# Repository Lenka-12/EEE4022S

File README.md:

# Audio Digitisation System 🎵

A high-performance audio digitization system built around the STM32F7 microcontroller, featuring dual Delta-Sigma ADCs (PCM1808 and ADAU1978) and an integrated ADC for comprehensive audio capture.

## 🎯 Overview

This project implements a complete audio digitization pipeline that captures audio data through multiple ADCs and transmits it to a PC for MATLAB-based analysis.

## 🔧 Hardware Components

### STM32F7 Nucleo Board
- Main processing unit
- Handles ADC interfacing and USB communication

### PCM1808 Delta-Sigma ADC ([Buy](https://www.aliexpress.com/item/32777376004.html))
- Stereo Audio ADC configuration
- Input: Bottom port MEMS microphone from DEVKIT-MEMS-001
- Signal conditioning via AD828 op-amp module ([AD828 Module Source](https://www.robotics.org.za/AD828A))
- I2S interface via SAI1 Block B
- 48 kHz sampling rate
- DMA circular mode operation

### Integrated ADC
- Input: Nucleo board pin A3
- Signal from top port MEMS microphone (DEVKIT-MEMS-001)
- Signal conditioning via BOB-09816 ([SparkFun BOB-09816](https://www.sparkfun.com/products/9816))
- Timer-triggered operation
- Circular DMA mode

### ADAU1978 Delta-Sigma ADC
- Integrated via [STEVAL-STWINMAV1](https://www.st.com/en/evaluation-tools/steval-stwinmav1.html) module
- TDM4 protocol through SAI1 Block A
- 24-bit resolution at 48 kHz
- DMA circular mode operation

> **Important Note**: When configuring SAI for TDM:
> - Clock strobing must be set to rising edge
> - Frame Synchro offset must be set before the First Bit

## 🔌 Communication

### USB Interface
- Protocol: USB Full Speed (FS) CDC
- Data transmission triggered by user button
- ADC activation controlled via Python script commands

## 💡 Status Indicators

| LED  | Function |
|------|----------|
| LD1  | Integrated ADC active |
| LD2  | PCM1808 active |
| LD3  | ADAU1978 active |

## 🛠️ Hardware Sources

### Microphones
- [DEVKIT-MEMS-001](https://www.sameskydevices.com/product/audio/microphones/development-kits/devkit-mems-001)
  - Bottom port MEMS mic → PCM1808
  - Top port MEMS mic → Integrated ADC

### Signal Conditioning
- PCM1808: [AD828 Op-amp Module](https://www.robotics.org.za/AD828A)
- Integrated ADC: [BOB-09816](https://www.sparkfun.com/products/9816)

### ADC Modules
- [PCM1808 Stereo Delta-Sigma ADC](https://www.aliexpress.com/item/32777376004.html)
- [STEVAL-STWINMAV1](https://www.st.com/en/evaluation-tools/steval-stwinmav1.html) (ADAU1978)
- STM32F7 Integrated ADC

## 📝 PCB Documentation

The repository includes:
- STEVAL-STWINMAV1 module adapter designs
- Audio Digitisation Hardware based on PCM1862 (production pending)
- 
## 📊 Data Analysis

MATLAB scripts are provided for processing the captured audio data. See the `/Processing` directory for analysis tools.

## 🤝 Contributing

Contributions are welcome! Please read our [Contributing Guide](CONTRIBUTING.md) for details on our code of conduct and the process for submitting pull requests.

## 📄 License

This project is licensed under the MIT License - see the [LICENSE](LICENSE) file for details.

## ✨ Acknowledgments

- STMicroelectronics for the STEVAL-STWINMAV1 reference design
- Same Sky for DEVKIT-MEMS-001
- SparkFun Electronics for BOB-09816
- Contributors and testers

---
*For technical questions and support, please open an issue in the repository.*

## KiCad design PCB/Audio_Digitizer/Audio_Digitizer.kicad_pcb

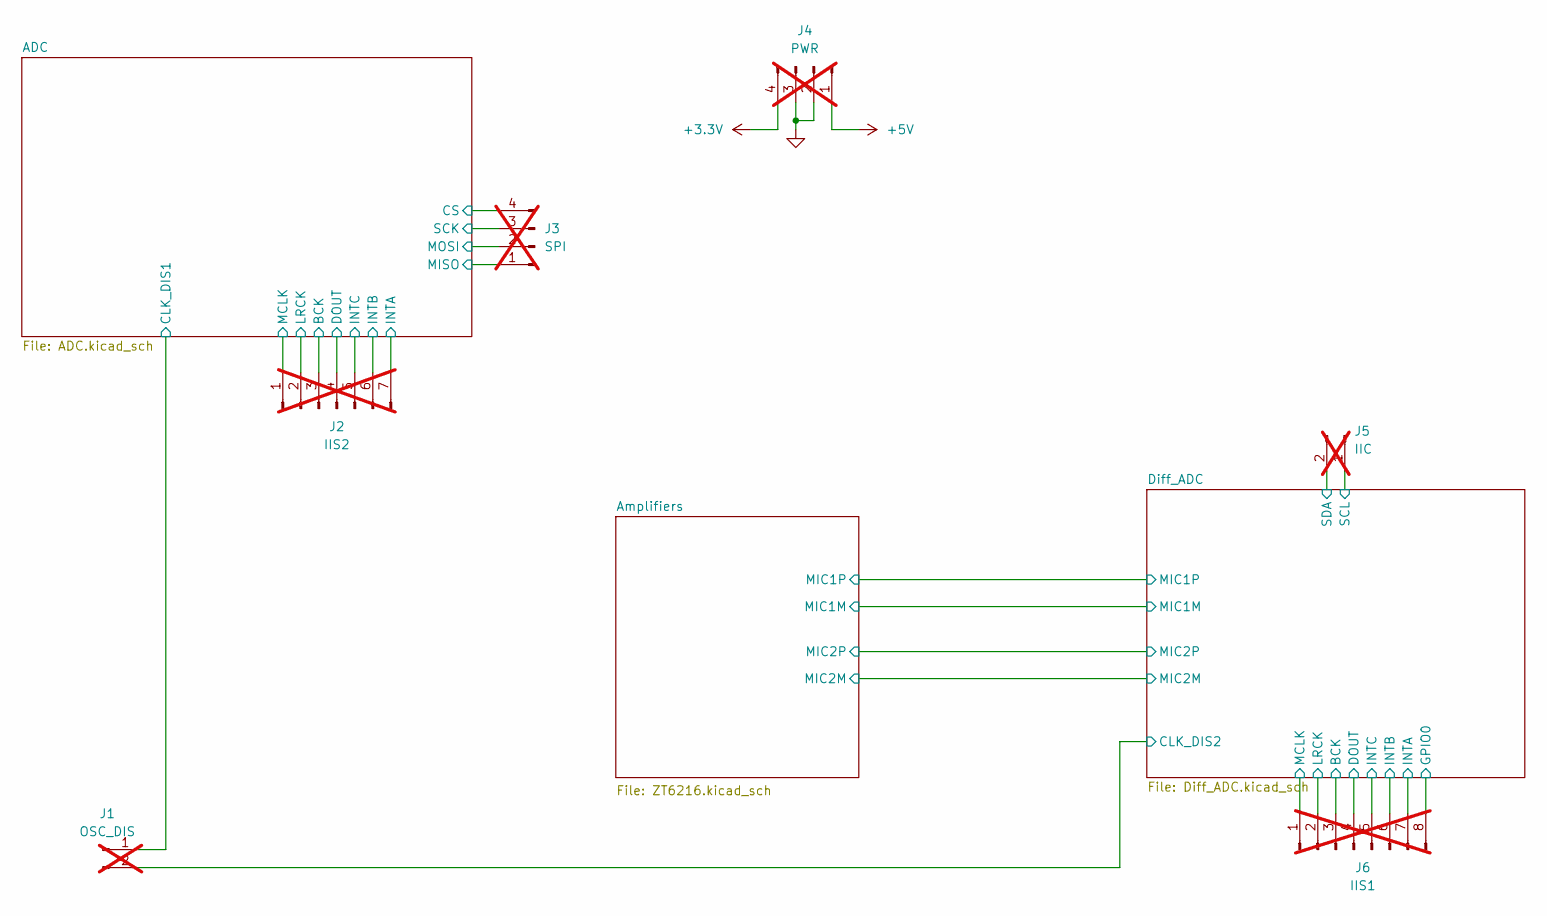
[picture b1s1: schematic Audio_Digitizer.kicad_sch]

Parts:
J1: OSC_DIS; PinHeader_1x02_P2.54mm_Vertical; not fitted
J2: IIS2; PinHeader_1x07_P2.54mm_Vertical; not fitted
J3: SPI; PinHeader_1x04_P2.54mm_Vertical; not fitted
J4: PWR; PinHeader_1x04_P2.54mm_Vertical; not fitted
J5: IIC; PinHeader_1x02_P2.54mm_Vertical; not fitted
J6: IIS1; PinHeader_1x08_P2.54mm_Vertical; not fitted

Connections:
+3.3V: J4.4; also elsewhere on the board
+5V: J4.1; also elsewhere on the board
/ADC/BCK: J2.3; also elsewhere on the board
/ADC/CLK_DIS1: J1.1; also elsewhere on the board
/ADC/CS: J3.4; also elsewhere on the board
/ADC/DOUT: J2.4; also elsewhere on the board
/ADC/INTA: J2.7; also elsewhere on the board
/ADC/INTB: J2.6; also elsewhere on the board
/ADC/INTC: J2.5; also elsewhere on the board
/ADC/LRCK: J2.2; also elsewhere on the board
/ADC/MCLK: J2.1; also elsewhere on the board
/ADC/MISO: J3.1; also elsewhere on the board
/ADC/MOSI: J3.2; also elsewhere on the board
/ADC/SCK: J3.3; also elsewhere on the board
/Diff_ADC/BCK: J6.3; also elsewhere on the board
/Diff_ADC/CLK_DIS2: J1.2; also elsewhere on the board
/Diff_ADC/DOUT: J6.4; also elsewhere on the board
/Diff_ADC/GPIO0: J6.8; also elsewhere on the board
/Diff_ADC/INTA: J6.7; also elsewhere on the board
/Diff_ADC/INTB: J6.6; also elsewhere on the board
/Diff_ADC/INTC: J6.5; also elsewhere on the board
/Diff_ADC/LRCK: J6.2; also elsewhere on the board
/Diff_ADC/MCLK: J6.1; also elsewhere on the board
/Diff_ADC/SCL: J5.1; also elsewhere on the board
/Diff_ADC/SDA: J5.2; also elsewhere on the board
GND: J4.2, J4.3; also elsewhere on the board

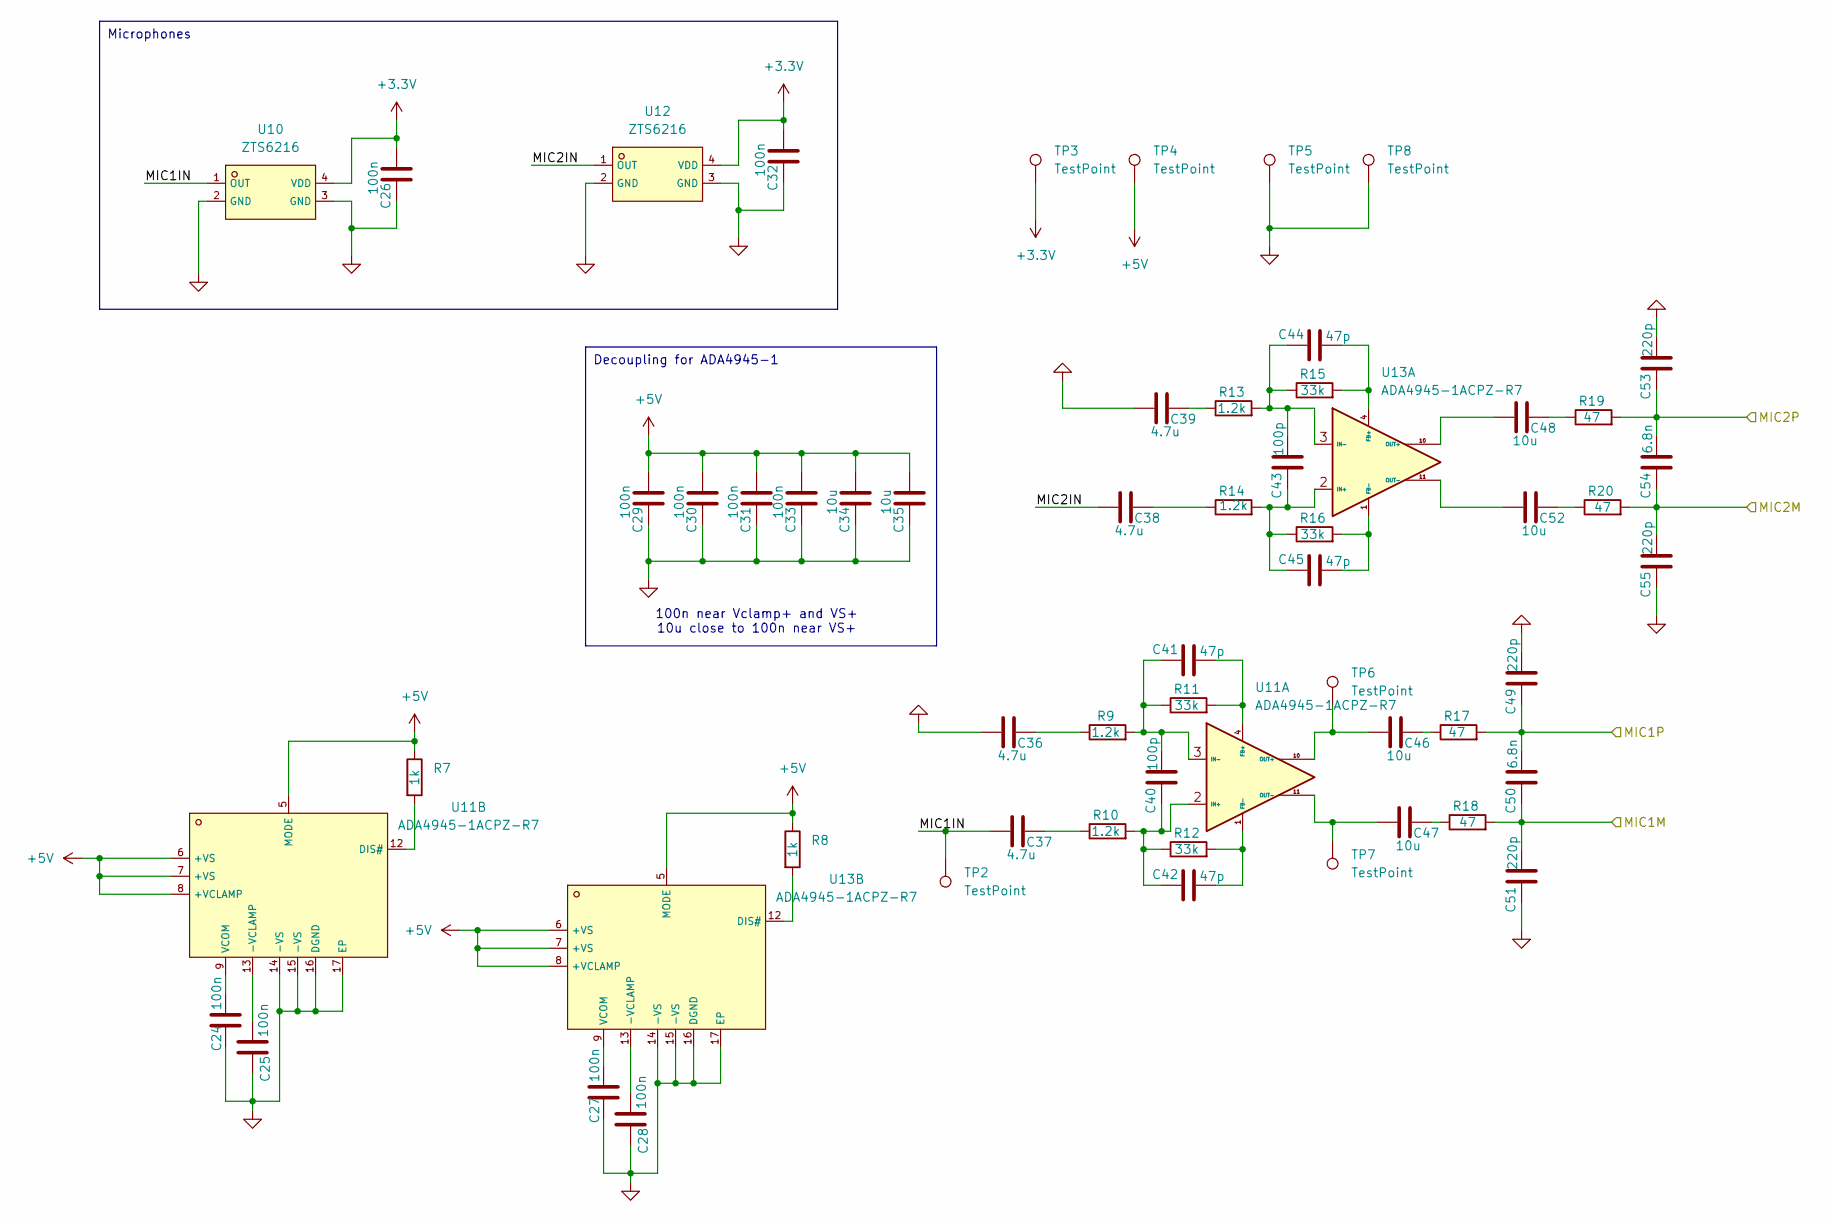
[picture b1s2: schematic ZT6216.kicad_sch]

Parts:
C24, C25, C26, C27, C28, C29, C30, C31, C32, C33: 100n; C_0402_1005Metric
C34, C35, C46, C47, C48, C52: 10u; C_0603_1608Metric
C36, C37, C38, C39: 4.7u; C_0402_1005Metric
C40, C43: 100p; C_0402_1005Metric
C41, C42, C44, C45: 47p; C_0402_1005Metric
C49, C51, C53, C55: 220p; C_0402_1005Metric
C50, C54: 6.8n; C_0603_1608Metric
R7, R8: 1k; R_0603_1608Metric
R9, R10, R13, R14: 1.2k; R_0402_1005Metric
R11, R12, R15, R16: 33k; R_0402_1005Metric
R17, R18, R19, R20: 47; R_0402_1005Metric
TP2, TP3, TP4, TP5, TP6, TP7, TP8: TestPoint; TestPoint_Pad_D1.5mm
U10, U12: ZTS6216; MIC-SMD_4P-L2.8-W1.9-P1.84-TL; LCSC C481302
U11, U13: ADA4945-1ACPZ-R7; LFCSP-16-1EP_3x3mm_P0.5mm_EP1.6x1.6mm; LCSC C560261

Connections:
+3.3V: C26.1, C32.1, TP3.1, U10.4 (VDD), U12.4 (VDD); also elsewhere on the board
+5V: C29.1, C30.1, C31.1, C33.1, C34.1, C35.1, R7.1, R8.1, TP4.1, U11.5 (MODE), U11.6 (+VS), U11.7 (+VS), U11.8 (+VCLAMP), U13.5 (MODE), U13.6 (+VS), U13.7 (+VS), U13.8 (+VCLAMP); also elsewhere on the board
/Amplifiers/MIC1IN: C37.1, TP2.1, U10.1 (OUT)
/Amplifiers/MIC1M: C50.1, C51.2, R18.2; also elsewhere on the board
/Amplifiers/MIC1P: C49.1, C50.2, R17.2; also elsewhere on the board
/Amplifiers/MIC2IN: C38.1, U12.1 (OUT)
/Amplifiers/MIC2M: C54.1, C55.2, R20.2; also elsewhere on the board
/Amplifiers/MIC2P: C53.1, C54.2, R19.2; also elsewhere on the board
GND: C24.1, C25.1, C26.2, C27.1, C28.1, C29.2, C30.2, C31.2, C32.2, C33.2, C34.2, C35.2, C36.1, C39.1, C49.2, C51.1, C53.2, C55.1, TP5.1, TP8.1, U10.2 (GND), U10.3 (GND), U11.14 (-VS), U11.15 (-VS), U11.16 (DGND), U11.17 (EP), U12.2 (GND), U12.3 (GND), U13.14 (-VS), U13.15 (-VS), U13.16 (DGND), U13.17 (EP); also elsewhere on the board
unnamed: C36.2, R9.1
unnamed: C37.2, R10.1
unnamed: C38.2, R14.1
unnamed: C39.2, R13.1
unnamed: C46.2, R17.1
unnamed: C47.2, R18.1
unnamed: C48.2, R19.1
unnamed: C52.2, R20.1
unnamed: C41.2, R11.2, U11.4 (FB+)
unnamed: C42.2, R12.2, U11.1 (FB-)
unnamed: C40.1, C42.1, R10.2, R12.1, U11.2 (IN+)
unnamed: C40.2, C41.1, R9.2, R11.1, U11.3 (IN-)
unnamed: C46.1, TP6.1, U11.10 (OUT+)
unnamed: C47.1, TP7.1, U11.11 (OUT-)
unnamed: C25.2, U11.13 (-VCLAMP)
unnamed: R7.2, U11.12 (DIS#)
unnamed: C24.2, U11.9 (VCOM)
unnamed: C44.2, R15.2, U13.4 (FB+)
unnamed: C45.2, R16.2, U13.1 (FB-)
unnamed: C43.1, C45.1, R14.2, R16.1, U13.2 (IN+)
unnamed: C43.2, C44.1, R13.2, R15.1, U13.3 (IN-)
unnamed: C48.1, U13.10 (OUT+)
unnamed: C52.1, U13.11 (OUT-)
unnamed: C28.2, U13.13 (-VCLAMP)
unnamed: R8.2, U13.12 (DIS#)
unnamed: C27.2, U13.9 (VCOM)

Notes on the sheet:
Decoupling for ADA4945-1
Microphones
100n near Vclamp+ and VS+ 10u close to 100n near VS+

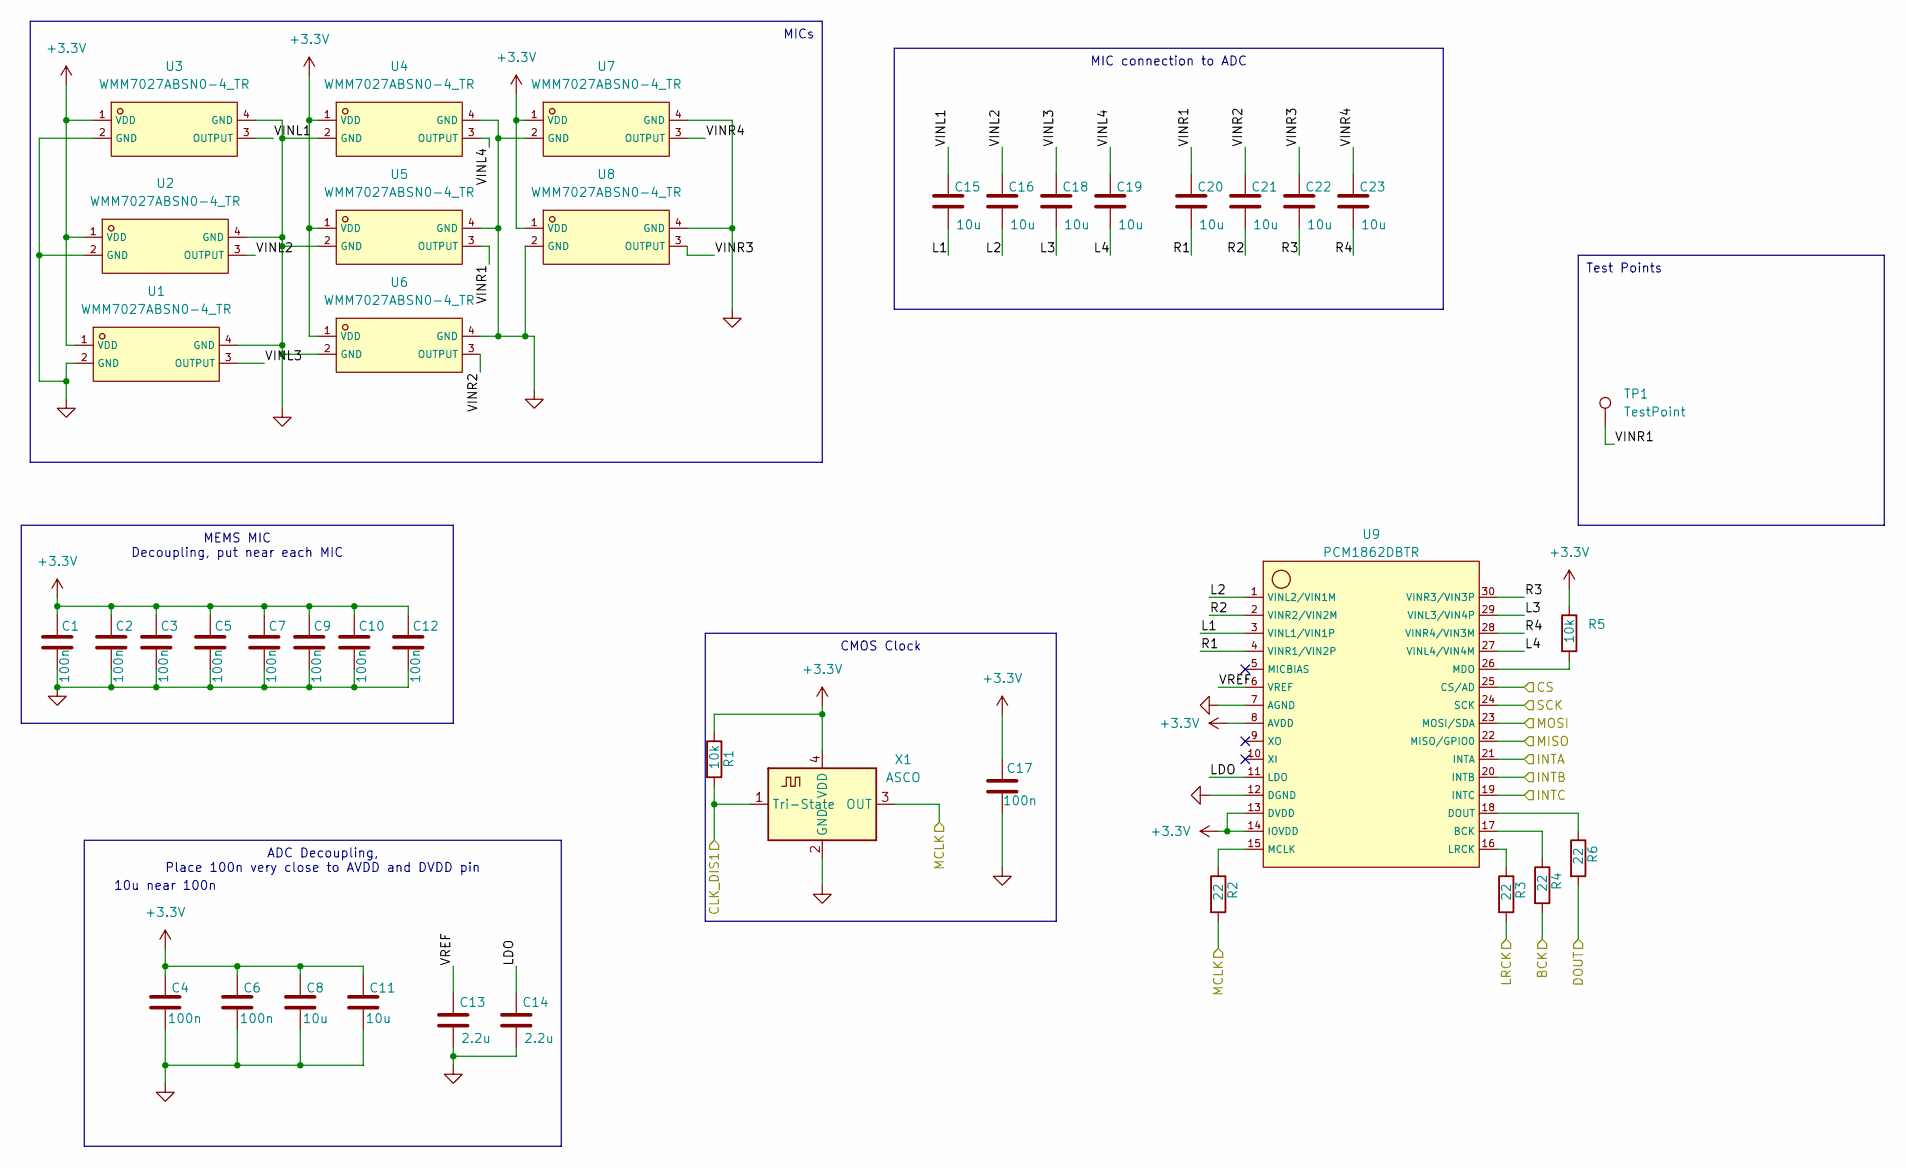
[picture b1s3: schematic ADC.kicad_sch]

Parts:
C1, C2, C3, C4, C5, C6, C7, C9, C10, C12, C17: 100n; C_0402_1005Metric
C8, C11, C15, C16, C18, C19, C20, C21, C22, C23: 10u; C_0603_1608Metric
C13, C14: 2.2u; C_0603_1608Metric
R1, R5: 10k; R_0402_1005Metric
R2, R3, R4, R6: 22; R_0402_1005Metric
TP1: TestPoint; TestPoint_Pad_D1.5mm
U1, U2, U3, U4, U5, U6, U7, U8: WMM7027ABSN0-4_TR; MIC-SMD_4P-L2.8-W1.9_MSM38A2718Z9BM3; LCSC C2931972
U9: PCM1862DBTR; TSSOP-30_4.4x7.8mm_P0.5mm
X1: ASCO; Crystal_SMD_3225-4Pin_3.2x2.5mm

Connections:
+3.3V: C1.1, C2.1, C3.1, C4.1, C5.1, C6.1, C7.1, C8.1, C9.1, C10.1, C11.1, C12.1, C17.1, R1.1, R5.1, U1.1 (VDD), U2.1 (VDD), U3.1 (VDD), U4.1 (VDD), U5.1 (VDD), U6.1 (VDD), U7.1 (VDD), U8.1 (VDD), U9.8 (AVDD), U9.13 (DVDD), U9.14 (IOVDD), X1.4 (VDD); also elsewhere on the board
/ADC/BCK: R4.2; also elsewhere on the board
/ADC/CLK_DIS1: R1.2, X1.1 (Tri-State); also elsewhere on the board
/ADC/CS: U9.25 (CS/AD); also elsewhere on the board
/ADC/DOUT: R6.2; also elsewhere on the board
/ADC/INTA: U9.21 (INTA); also elsewhere on the board
/ADC/INTB: U9.20 (INTB); also elsewhere on the board
/ADC/INTC: U9.19 (INTC); also elsewhere on the board
/ADC/L1: C15.2, U9.3 (VINL1/VIN1P)
/ADC/L2: C16.2, U9.1 (VINL2/VIN1M)
/ADC/L3: C18.2, U9.29 (VINL3/VIN4P)
/ADC/L4: C19.2, U9.27 (VINL4/VIN4M)
/ADC/LDO: C14.1, U9.11 (LDO)
/ADC/LRCK: R3.2; also elsewhere on the board
/ADC/MCLK: R2.2, X1.3 (OUT); also elsewhere on the board
/ADC/MISO: U9.22 (MISO/GPIO0); also elsewhere on the board
/ADC/MOSI: U9.23 (MOSI/SDA); also elsewhere on the board
/ADC/R1: C20.2, U9.4 (VINR1/VIN2P)
/ADC/R2: C21.2, U9.2 (VINR2/VIN2M)
/ADC/R3: C22.2, U9.30 (VINR3/VIN3P)
/ADC/R4: C23.2, U9.28 (VINR4/VIN3M)
/ADC/SCK: U9.24 (SCK); also elsewhere on the board
/ADC/VINL1: C15.1, U3.3 (OUTPUT)
/ADC/VINL2: C16.1, U2.3 (OUTPUT)
/ADC/VINL3: C18.1, U1.3 (OUTPUT)
/ADC/VINL4: C19.1, U4.3 (OUTPUT)
/ADC/VINR1: C20.1, TP1.1, U5.3 (OUTPUT)
/ADC/VINR2: C21.1, U6.3 (OUTPUT)
/ADC/VINR3: C22.1, U8.3 (OUTPUT)
/ADC/VINR4: C23.1, U7.3 (OUTPUT)
/ADC/VREF: C13.1, U9.6 (VREF)
GND: C1.2, C2.2, C3.2, C4.2, C5.2, C6.2, C7.2, C8.2, C9.2, C10.2, C11.2, C12.2, C13.2, C14.2, C17.2, U1.2 (GND), U1.4 (GND), U2.2 (GND), U2.4 (GND), U3.2 (GND), U3.4 (GND), U4.2 (GND), U4.4 (GND), U5.2 (GND), U5.4 (GND), U6.2 (GND), U6.4 (GND), U7.2 (GND), U7.4 (GND), U8.2 (GND), U8.4 (GND), U9.7 (AGND), U9.12 (DGND), X1.2 (GND); also elsewhere on the board
unnamed: R4.1, U9.17 (BCK)
unnamed: R6.1, U9.18 (DOUT)
unnamed: R3.1, U9.16 (LRCK)
unnamed: R2.1, U9.15 (MCLK)
unnamed: R5.2, U9.26 (MDO)

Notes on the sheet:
CMOS Clock
MICs
Test Points
ADC Decoupling, Place 100n very close to AVDD and DVDD pin
MEMS MIC Decoupling, put near each MIC
MIC connection to ADC
10u near 100n

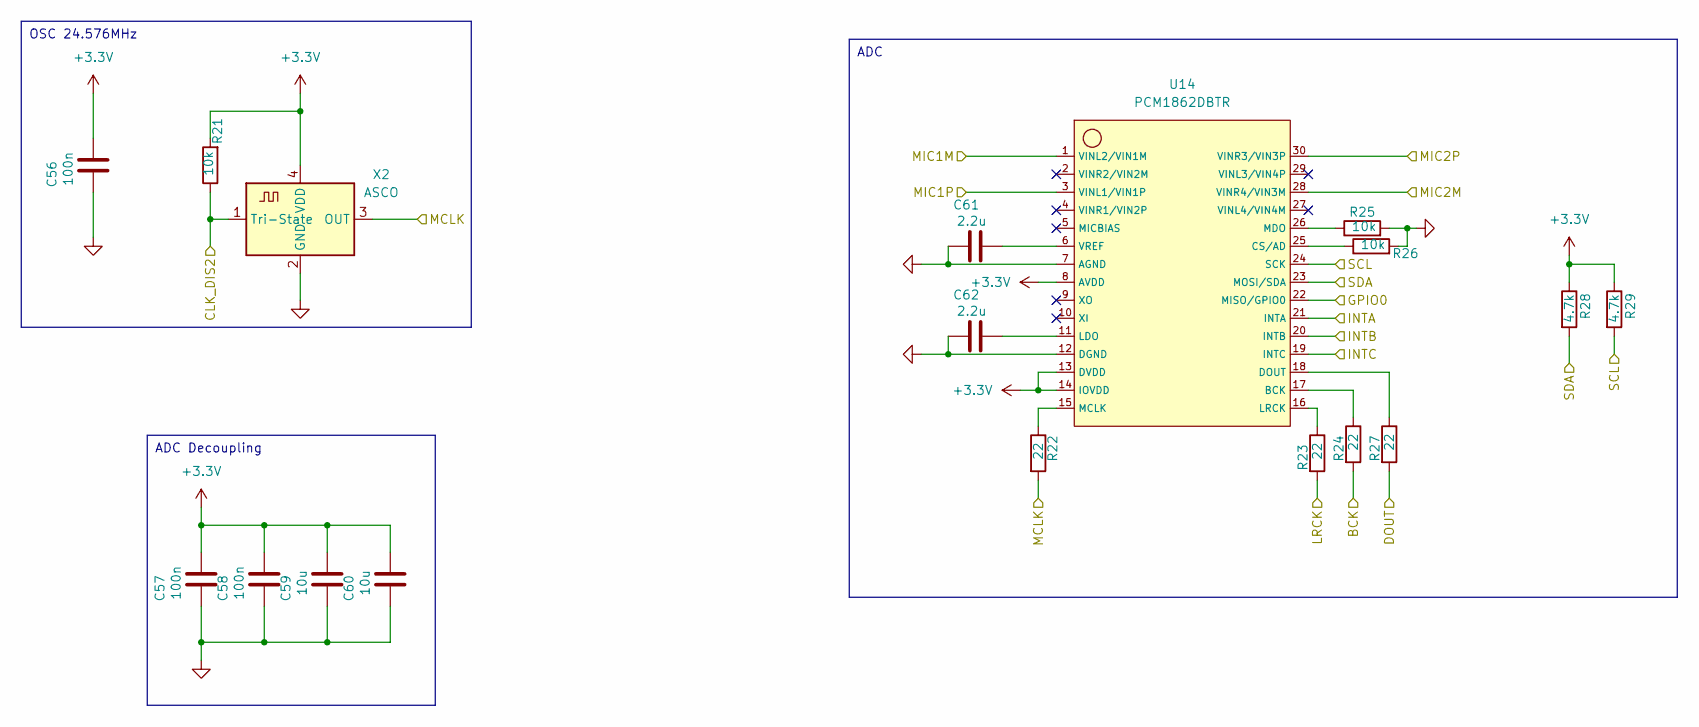
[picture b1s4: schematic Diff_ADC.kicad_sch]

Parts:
C56, C57, C58: 100n; C_0402_1005Metric
C59, C60: 10u; C_0603_1608Metric
C61, C62: 2.2u; C_0603_1608Metric
R21, R25, R26: 10k; R_0402_1005Metric
R22, R23, R24, R27: 22; R_0402_1005Metric
R28, R29: 4.7k; R_0402_1005Metric
U14: PCM1862DBTR; TSSOP-30_4.4x7.8mm_P0.5mm
X2: ASCO; Crystal_SMD_3225-4Pin_3.2x2.5mm

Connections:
+3.3V: C56.2, C57.2, C58.2, C59.2, C60.2, R21.2, R28.1, R29.1, U14.8 (AVDD), U14.13 (DVDD), U14.14 (IOVDD), X2.4 (VDD); also elsewhere on the board
/Amplifiers/MIC1M: U14.1 (VINL2/VIN1M); also elsewhere on the board
/Amplifiers/MIC1P: U14.3 (VINL1/VIN1P); also elsewhere on the board
/Amplifiers/MIC2M: U14.28 (VINR4/VIN3M); also elsewhere on the board
/Amplifiers/MIC2P: U14.30 (VINR3/VIN3P); also elsewhere on the board
/Diff_ADC/BCK: R24.2; also elsewhere on the board
/Diff_ADC/CLK_DIS2: R21.1, X2.1 (Tri-State); also elsewhere on the board
/Diff_ADC/DOUT: R27.2; also elsewhere on the board
/Diff_ADC/GPIO0: U14.22 (MISO/GPIO0); also elsewhere on the board
/Diff_ADC/INTA: U14.21 (INTA); also elsewhere on the board
/Diff_ADC/INTB: U14.20 (INTB); also elsewhere on the board
/Diff_ADC/INTC: U14.19 (INTC); also elsewhere on the board
/Diff_ADC/LRCK: R23.2; also elsewhere on the board
/Diff_ADC/MCLK: R22.2, X2.3 (OUT); also elsewhere on the board
/Diff_ADC/SCL: R29.2, U14.24 (SCK); also elsewhere on the board
/Diff_ADC/SDA: R28.2, U14.23 (MOSI/SDA); also elsewhere on the board
GND: C56.1, C57.1, C58.1, C59.1, C60.1, C61.1, C62.1, R25.2, R26.2, U14.7 (AGND), U14.12 (DGND), X2.2 (GND); also elsewhere on the board
unnamed: R24.1, U14.17 (BCK)
unnamed: R26.1, U14.25 (CS/AD)
unnamed: R27.1, U14.18 (DOUT)
unnamed: C62.2, U14.11 (LDO)
unnamed: R23.1, U14.16 (LRCK)
unnamed: R22.1, U14.15 (MCLK)
unnamed: R25.1, U14.26 (MDO)
unnamed: C61.2, U14.6 (VREF)

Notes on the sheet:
OSC 24.576MHz
ADC Decoupling
ADC

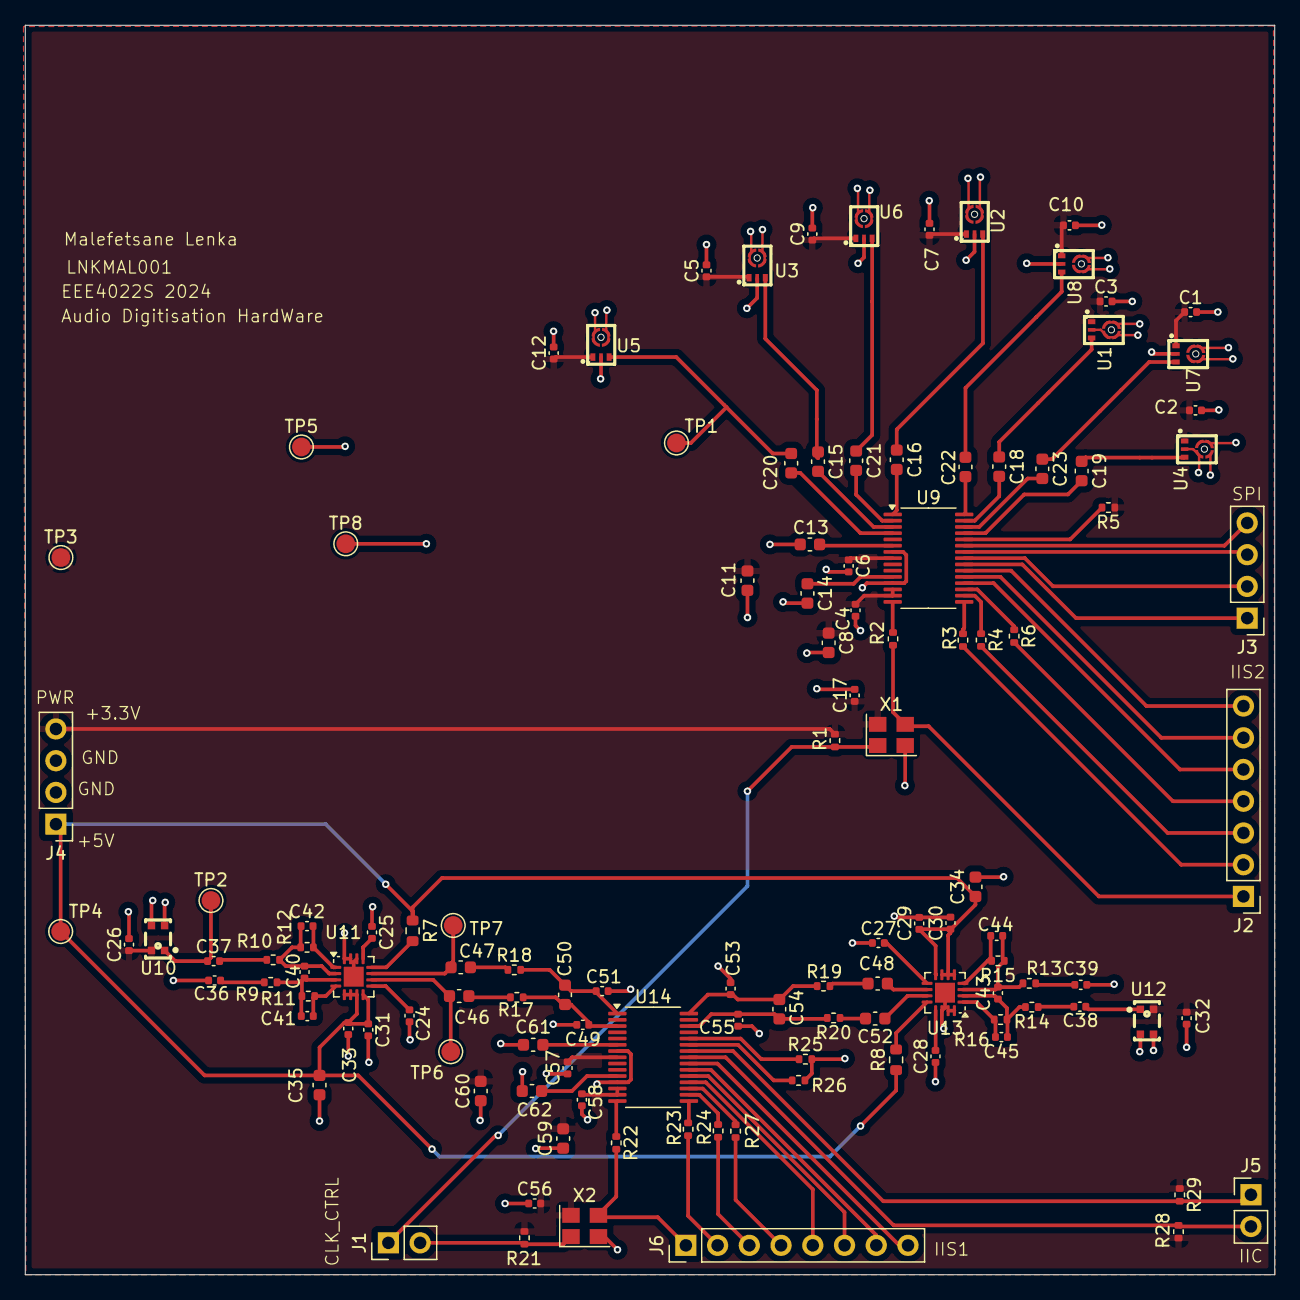
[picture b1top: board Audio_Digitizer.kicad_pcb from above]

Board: 2 copper layers, 100.0 x 100.0 mm, 121 parts (0 on the bottom side), 89 nets.

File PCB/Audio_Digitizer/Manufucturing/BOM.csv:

"Reference","Value","Footprint","DNP","LCSC"
"C1,C2,C3,C4,C5,C6,C7,C9,C10,C12,C17,C24,C25,C26,C27,C28,C29,C30,C31,C32,C33,C56,C57,C58","100n","Capacitor_SMD:C_0402_1005Metric","",""
"C8,C11,C15,C16,C18,C19,C20,C21,C22,C23,C34,C35,C46,C47,C48,C52,C59,C60","10u","Capacitor_SMD:C_0603_1608Metric","",""
"C13,C14,C61,C62","2.2u","Capacitor_SMD:C_0603_1608Metric","",""
"C36,C37,C38,C39","4.7u","Capacitor_SMD:C_0402_1005Metric","",""
"C40,C43","100p","Capacitor_SMD:C_0402_1005Metric","",""
"C41,C42,C44,C45","47p","Capacitor_SMD:C_0402_1005Metric","",""
"C49,C51,C53,C55","220p","Capacitor_SMD:C_0402_1005Metric","",""
"C50,C54","6.8n","Capacitor_SMD:C_0603_1608Metric","",""
"J1","OSC_DIS","Connector_PinHeader_2.54mm:PinHeader_1x02_P2.54mm_Vertical","DNP",""
"J2","IIS2","Connector_PinHeader_2.54mm:PinHeader_1x07_P2.54mm_Vertical","DNP",""
"J3","SPI","Connector_PinHeader_2.54mm:PinHeader_1x04_P2.54mm_Vertical","DNP",""
"J4","PWR","Connector_PinHeader_2.54mm:PinHeader_1x04_P2.54mm_Vertical","DNP",""
"J5","IIC","Connector_PinHeader_2.54mm:PinHeader_1x02_P2.54mm_Vertical","DNP",""
"J6","IIS1","Connector_PinHeader_2.54mm:PinHeader_1x08_P2.54mm_Vertical","DNP",""
"R1,R5,R21,R25,R26","10k","Resistor_SMD:R_0402_1005Metric","",""
"R2,R3,R4,R6,R22,R23,R24,R27","22","Resistor_SMD:R_0402_1005Metric","",""
"R7,R8","1k","Resistor_SMD:R_0603_1608Metric","",""
"R9,R10,R13,R14","1.2k","Resistor_SMD:R_0402_1005Metric","",""
"R11,R12,R15,R16","33k","Resistor_SMD:R_0402_1005Metric","",""
"R17,R18,R19,R20","47","Resistor_SMD:R_0402_1005Metric","",""
"R28,R29","4.7k","Resistor_SMD:R_0402_1005Metric","",""
"TP1,TP2,TP3,TP4,TP5,TP6,TP7,TP8","TestPoint","TestPoint:TestPoint_Pad_D1.5mm","",""
"U1,U2,U3,U4,U5,U6,U7,U8","WMM7027ABSN0-4_TR","footprints:MIC-SMD_4P-L2.8-W1.9_MSM38A2718Z9BM3","","C2931972"
"U9,U14","PCM1862DBTR","Package_SO:TSSOP-30_4.4x7.8mm_P0.5mm","",""
"U10,U12","ZTS6216","footprints:MIC-SMD_4P-L2.8-W1.9-P1.84-TL","","C481302"
"U11,U13","ADA4945-1ACPZ-R7","Package_CSP:LFCSP-16-1EP_3x3mm_P0.5mm_EP1.6x1.6mm","","C560261"
"X1,X2","ASCO","Crystal:Crystal_SMD_3225-4Pin_3.2x2.5mm","",""

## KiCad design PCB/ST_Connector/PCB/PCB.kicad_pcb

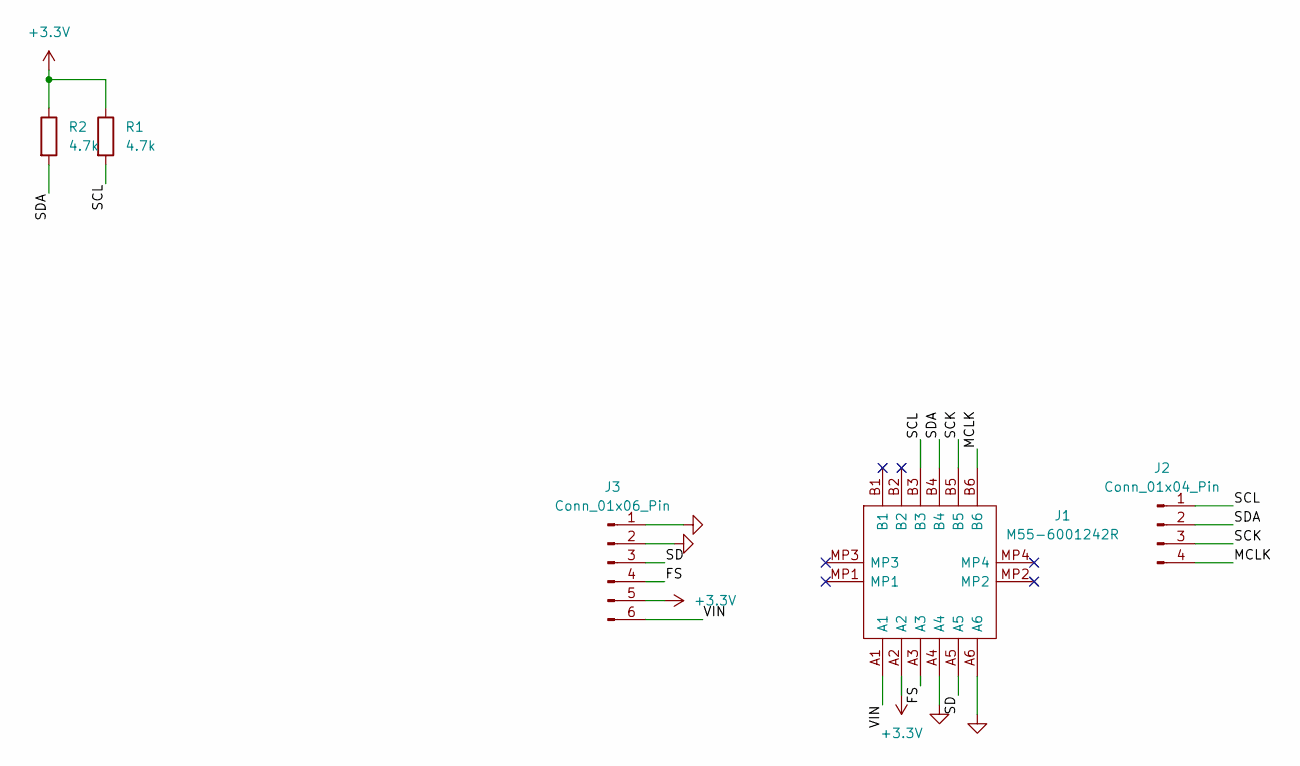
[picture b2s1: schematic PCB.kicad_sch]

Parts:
J1: M55-6001242R; M556001242R; Manufacturer_Part_Number M55-6001242R; Mouser Part Number 855-M55-6001242R
J2: Conn_01x04_Pin; PinHeader_1x04_P2.54mm_Vertical
J3: Conn_01x06_Pin; PinHeader_1x06_P2.54mm_Vertical
R1, R2: 4.7k; R_Axial_DIN0204_L3.6mm_D1.6mm_P5.08mm_Horizontal

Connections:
+3.3V: J1.A2, J3.5, R1.1, R2.1
/FS: J1.A3, J3.4
/MCLK: J1.B6, J2.4
/SCK: J1.B5, J2.3
/SCL: J1.B3, J2.1, R1.2
/SD: J1.A5, J3.3
/SDA: J1.B4, J2.2, R2.2
/VIN: J1.A1, J3.6
GND: J1.A4, J1.A6, J3.1, J3.2

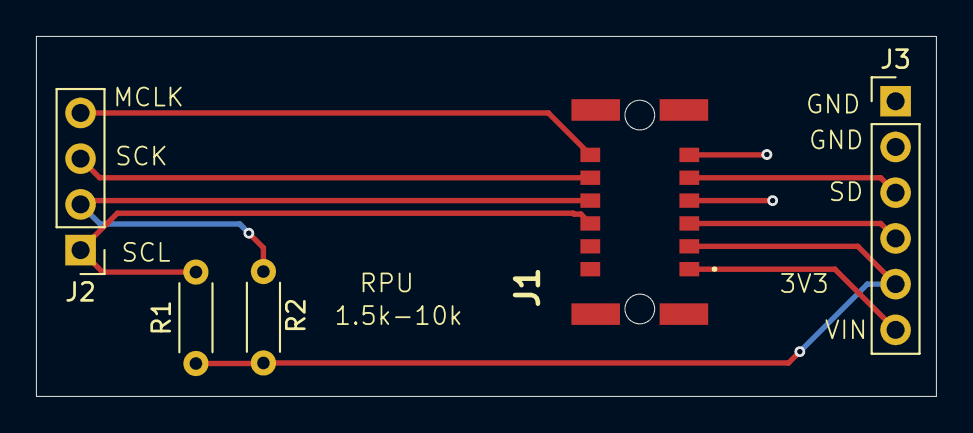
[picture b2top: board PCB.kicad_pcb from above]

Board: 2 copper layers, 50.0 x 20.0 mm, 5 parts (0 on the bottom side), 9 nets.

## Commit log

2024-10-28 PCB added
2024-10-30 remove unnecessary files

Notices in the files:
README.md:
License: MIT
